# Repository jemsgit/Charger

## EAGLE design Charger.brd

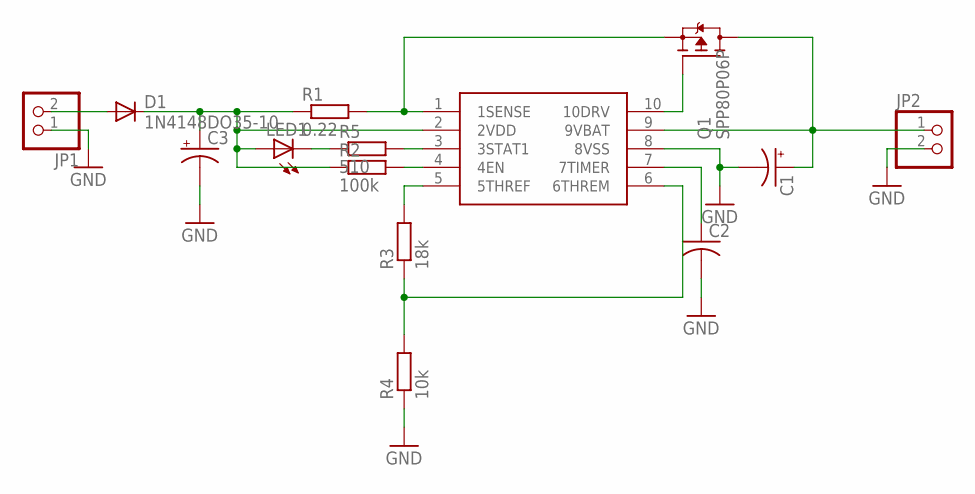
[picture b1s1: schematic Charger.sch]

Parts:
C1, C3: CPOL-US153CLV-0505; 153CLV-0505
C2: C-USC0805; C0805
D1: 1N4148DO35-10; DO35-10
JP1, JP2: PINHD-1X2; 1X02
LED1: LEDCHIPLED_1206; CHIPLED_1206
Q1: SPP80P06P; TO220
R1: 0.22; R0805
R2: 100k; R0805
R3: 18k; R0805
R4: 10k; R0805
R5: 510; R0805
U$1: MCP73841; MSOP10

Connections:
GND: C1.-, C2.2, C3.-, JP1.1, JP2.2, R4.1, U$1.8 (8VSS)
unnamed: C3.+, D1.C, LED1.A, R1.1, R2.1, U$1.2 (2VDD)
unnamed: Q1.3 (S), R1.2, U$1.1 (1SENSE)
unnamed: R2.2, U$1.4 (4EN)
unnamed: LED1.C, R5.1
unnamed: Q1.1 (G), U$1.10 (10DRV)
unnamed: R5.2, U$1.3 (3STAT1)
unnamed: C1.+, JP2.1, Q1.2 (D), U$1.9 (9VBAT)
unnamed: C2.1, U$1.7 (7TIMER)
unnamed: D1.A, JP1.2
unnamed: R3.2, U$1.5 (5THREF)
unnamed: R3.1, R4.2, U$1.6 (6THREM)

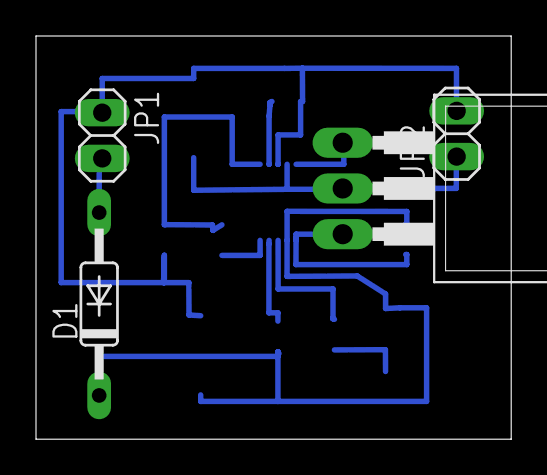
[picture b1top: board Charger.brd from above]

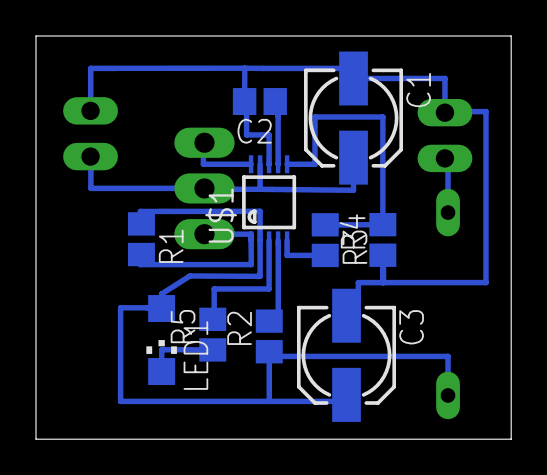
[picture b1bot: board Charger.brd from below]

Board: 2 copper layers, 26.4 x 22.4 mm, 14 parts (10 on the bottom side), 12 nets.

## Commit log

2014-12-19 Add schematic
2014-12-19 Add board
2014-12-19 Finished BRD
2014-12-22 Add values of capacitors and parallel resistors
2014-12-22 Revert "Add values of capacitors and parallel resistors"
    This reverts commit c5449c38890c53df2ecf398a39eaa116fb527d7b.
2014-12-22 Add values
